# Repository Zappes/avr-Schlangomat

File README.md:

Der Schlangomat
===============

Was ist das?
------------
Der Schlangomat ist eine Kiste mit etwas Elektronik, ein paar Relais und zwei kombinierten Feuchtigkeits- und Temperatursensoren.
In der Kiste sind Steckdosen verbaut, die über Relais anhand gewisser Regeln an- und ausgeschaltet werden. Zusätzlich kann der
aktuelle Zustand der Dosen und Sensoren per WLAN abgefragt werden und die verschiedenen Betriebsparameter können mit einem
seriellen Terminal per USB programmiert werden.

Gedacht ist das ganze
als "Proof of Concept" für die Klimatisierung von Terrarien mit Schlangen drin - natürlich nur als Test und auf gar keinen fickenden
Fall für den tatsächlichen Einsatz. Ich bin schließlich kein Elektriker und baue deswegen keine Geräte, die mit Netzspannung
betrieben werden.

Was steckt so drin?
-------------------
Der Mikrocontroller ist ein ATmega32U4 von Atmel, der den USB-Controller schon drin hat. Für die WLAN-Anbindung wird ein ESP8266-03-Modul
benutzt, das mit der ganz normalen AT-Firmware läuft. Die Relais sind 36.11-Relais von Finder, die von einem ULN2003A angesteuert werden.

Output per http
---------------
Wenn man per http auf die IP des Geräts zugreift, kriegt man den folgenden Output zurück:

```
{"sock":[0,0,0,0],"sens":[{"h":45.9,"t":25.9,"e":0,"c":0},{"h":46.7,"t":26.2,"e":0,"c":0}],"rule":["T1 15 18","H1 32 38","T2 21 26","H2 34 50"]}
```

- sock: Der Zustand der Steckdosen von Dose 1 bis Dose 4. Im Beispiel ist nur die 3 an.
- sens: Die aktuellen Messwerte. h steht für die relative Luftfeuchtigkeit in Prozent, t für die Temperatur in °C, e für einen Errocode und c dafür, wie fot dieser Fehler jetzt in Folge aufgetreten ist.
- rule: Die aktuellen Regeln von Dose 1 bis Dose 4. Mehr dazu weiter unten.

Das Mistding schickt wirklich nur diesen Output, keine HTTP-Header. Hintergrund ist schlicht und ergreifend ein Bug in der
Firmware des WLAN-Moduls, wegen dem es nicht möglich ist, CRLF-Sequenzen zu schicken. Wer eine Lösung dafür findet, möge bitte
einen Pull-Request schicken ...

Intern werden die Sensoren nur etwa alle 5 Sekunden abgefragt. Wenn bei der Abfrage ein Fehler auftritt, steht dieser im Errorcode des Ergebnisses,
als Temperatur und Feuchtigkeit werden dann jeweils 0.0 gemeldet. Wenn der Fehler bei mehreren Abfragen in Forlge auftritt, steht in c die Anzahl
dieser Fehlversuche oder 255, wenn es schon mehr als 254 mal passiert ist. Was die genauen Fehlercodes bedeuten, kann man sich in lib/am2302.c
raussuchen, bei Code 4 kann man aber meistens davon ausgehen, dass der Sensor schlicht nicht eingesteckt ist. Oder total im Arsch.

USB-Kommandos
-------------

Wenn man ein USB-Kabel in das Gerät pöppelt, kann man sich mit einem seriellen Terminal verbinden. Als Verbindungsparameter sind 9600 8N1 zu verwenden, lokales Echo kann man sich schenken. Linuxer können das
beispielsweise so angehen:

```
minicom --device /dev/ttyACM0 -b 9600
```

Windowser verwenden vermutlich Putty oder Teraterm oder sowas.

In der seriellen Konsole hat man nun die folgenden Befehle:

| Befehl      | Parameter        | Beschreibung
|-------------|------------------|-------------
| espsetup    |                  | Initialisiert den WLAN-Chip.
| esp         | esp-kommando     | Führt ein ESP-Kommando aus - siehe weiter unten.
| setrule     | dose [regel]     | Setzt eine Regel für eine Dose, z.b. mit "setrule 1 T1 23 27". Ohne Regel wird die Regelausführung für die Dose deaktiviert
| getrule     | [dose]           | Gibt eine Regel aus. Ohne Parameter werden alle Regeln ausgegeben.
| on          | [dose]           | Schaltet eine Dose an. Wird die Dose nicht angegeben, werden alle Dosen aktiviert.
| off         | [dose]           | Schaltet eine Dose ab. Wird die Dose nicht angegeben, werden alle Dosen deaktiviert.
| state       |                  | Gibt den aktuellen Zustand der Dosen aus.
| sens        |                  | Gibt den aktuellen Zustand der Sensoren aus.
| setinterval | Sekunden         | Setzt das Intervall, in dem die Sensoren abgefragt und die Regeln ausgeführt werden.
| getinterval | Sekunden         | Zeigt das Intervall, in dem die Sensoren abgefragt und die Regeln ausgeführt werden, an.

Die Regelsyntax
---------------

Die Regeln beziehen sich immer auf eine Steckdose und können die jeweilige Dose abhängig von der Temperatur oder Luftfeuchtigkeit eines der beiden Sensoren messen. Das Format beim Setzen der Regel ist wie folgt:

```
setrule [Dose] [T|H][Sensor] [Minimum] [Maximum]
```

Angenommen, an Dose 3 hängt eine Heizung für das Terrarium, in dem Sensor 2 angebracht ist. Nun soll eine Regel die Temperatur zwischen 25 und 28 °C halten. Der entsprechende Befehl sieht wie folgt aus:

```
setrule 3 T2 25 28
```

Dabei ist zu beachten, dass die Firmware derzeit davon ausgeht, dass die Geräte an den Dosen die Messwerte ERHÖHEN, d.h. wie eine Heizung oder ein Befeuchter funktionieren. Würde man Kühlungen oder Entfeuchter anschließen wollen, wäre eine Firmware nötig, bei der man angeben kann, welche Wirkung die Geräte haben.

Die ESP-Befehle
---------------

Mit dem Befehl "esp" können Befehle an den ESP-Chip durchgereicht werden. Dabei ist zu beachten, dass das nur für die "normalen" Befehle funktioniert, die am Ende "OK" oder "ERR" ausgeben. Kompliziertes Zeug wie CIPSEND funktioniert so nicht, und die Ausgabe beim Reset ist zumindest eigentümlich.

Typischerweise braucht man die ESP-Befehle sowieso nur, um sich mit einem WLAN-AP zu verbinden. Dafür zeigt man sich erst mal mit ESP AT+CWLAP die Namen der APs an, dann verbindet man sich mittels ESP AT+CWJAP="SSID","PASS".

Die Frontplatte
---------------

Die Beschaltung der Frontplatte ist wie folgt:

Gibt es Videos?
-----------------------
[Natürlich gibt es eine Youtube-Playlist.](https://www.youtube.com/playlist?list=PLFFlJlvZ--PkRfQQ3qQJbDEAugWxiXpbW)

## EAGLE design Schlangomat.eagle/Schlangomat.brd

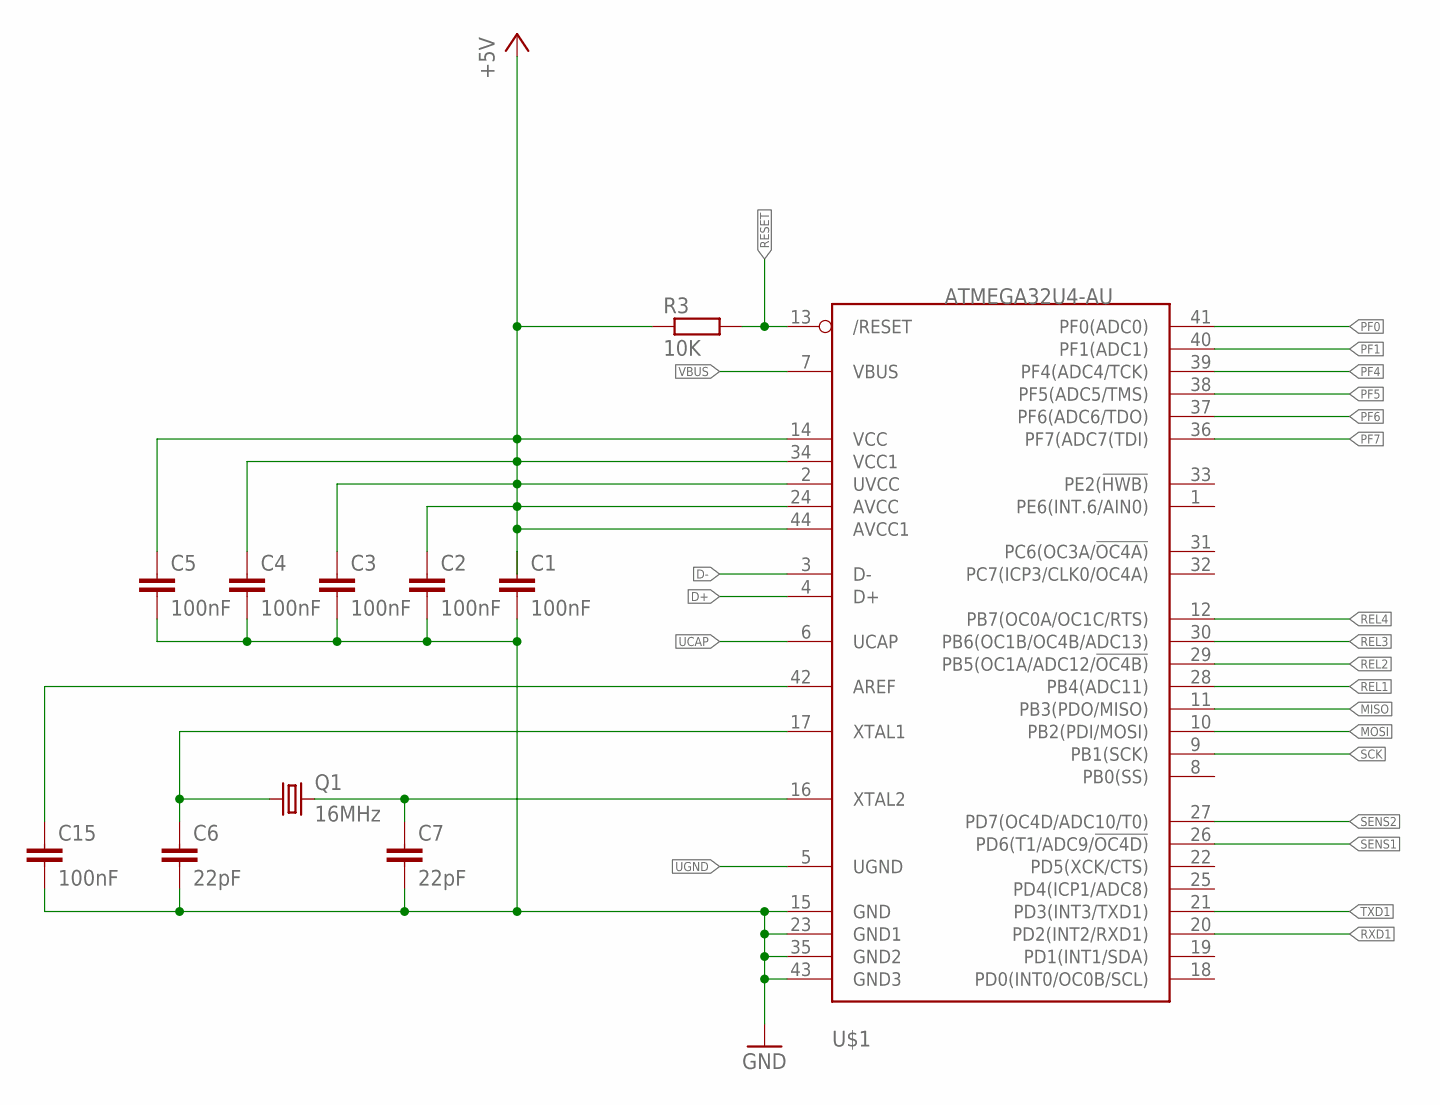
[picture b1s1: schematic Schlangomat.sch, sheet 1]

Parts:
C1, C2, C3, C4, C5, C15: 100nF; C0805
C6, C7: 22pF; C0805
Q1: 16MHz; HC49/S
R3: 10K; R0805
U$1: ATMEGA32U4-AU; TQFP44

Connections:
+5V: C1.1, C2.1, C3.1, C4.1, C5.1, R3.1, U$1.2 (UVCC), U$1.14 (VCC), U$1.24 (AVCC), U$1.34 (VCC1), U$1.44 (AVCC1); also elsewhere on the board
D+: U$1.4 (D+); also elsewhere on the board
D-: U$1.3 (D-); also elsewhere on the board
GND: C1.2, C2.2, C3.2, C4.2, C5.2, C6.2, C7.2, C15.2, U$1.15 (GND), U$1.23 (GND1), U$1.35 (GND2), U$1.43 (GND3); also elsewhere on the board
MISO: U$1.11 (PB3(PDO/MISO)); also elsewhere on the board
MOSI: U$1.10 (PB2(PDI/MOSI)); also elsewhere on the board
unnamed: C6.1, Q1.1, U$1.17 (XTAL1)
unnamed: C7.1, Q1.2, U$1.16 (XTAL2)
unnamed: C15.1, U$1.42 (AREF)
PF0: U$1.41 (PF0(ADC0)); also elsewhere on the board
PF1: U$1.40 (PF1(ADC1)); also elsewhere on the board
PF4: U$1.39 (PF4(ADC4/TCK)); also elsewhere on the board
PF5: U$1.38 (PF5(ADC5/TMS)); also elsewhere on the board
PF6: U$1.37 (PF6(ADC6/TDO)); also elsewhere on the board
PF7: U$1.36 (PF7(ADC7(TDI)); also elsewhere on the board
REL1: U$1.28 (PB4(ADC11)); also elsewhere on the board
REL2: U$1.29 (PB5(OC1A/ADC12/!OC4B)); also elsewhere on the board
REL3: U$1.30 (PB6(OC1B/OC4B/ADC13)); also elsewhere on the board
REL4: U$1.12 (PB7(OC0A/OC1C/RTS)); also elsewhere on the board
RESET: R3.2, U$1.13 (/RESET); also elsewhere on the board
RXD1: U$1.20 (PD2(INT2/RXD1)); also elsewhere on the board
SCK: U$1.9 (PB1(SCK)); also elsewhere on the board
SENS1: U$1.26 (PD6(T1/ADC9/!OC4D)); also elsewhere on the board
SENS2: U$1.27 (PD7(OC4D/ADC10/T0)); also elsewhere on the board
TXD1: U$1.21 (PD3(INT3/TXD1)); also elsewhere on the board
UCAP: U$1.6 (UCAP); also elsewhere on the board
UGND: U$1.5 (UGND); also elsewhere on the board
VBUS: U$1.7 (VBUS); also elsewhere on the board

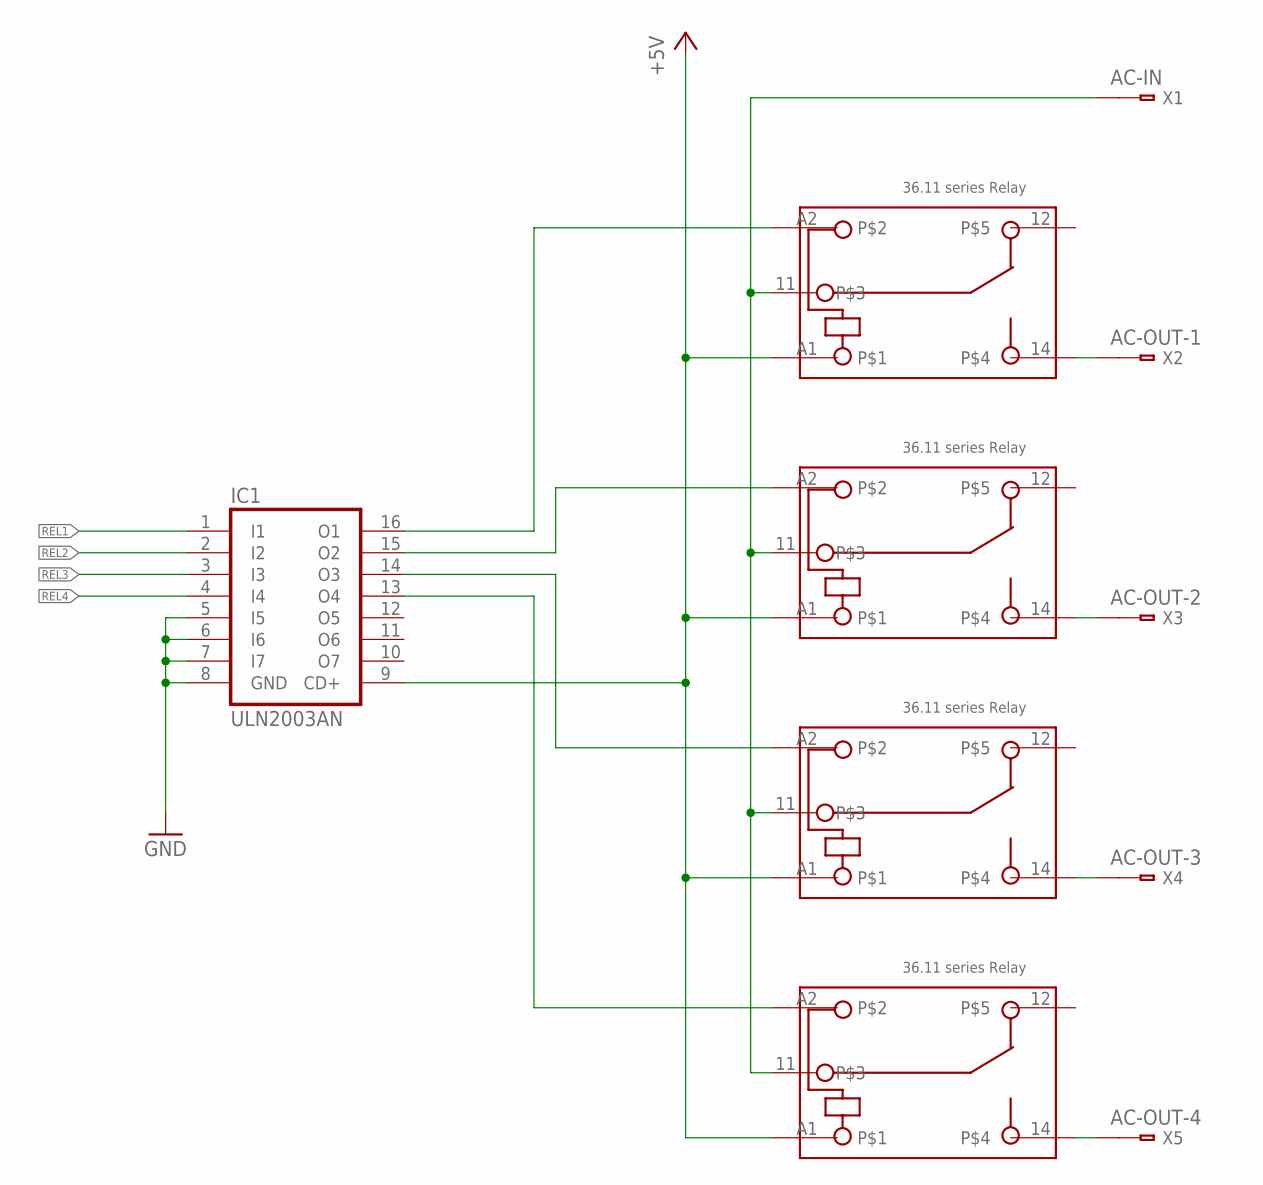
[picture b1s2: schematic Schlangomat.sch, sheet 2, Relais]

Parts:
IC1: ULN2003AN; DIL16
K1, K2, K3, K4: 36.11
X1: AC-IN; 236-5XX
X2: AC-OUT-1; 236-5XX
X3: AC-OUT-2; 236-5XX
X4: AC-OUT-3; 236-5XX
X5: AC-OUT-4; 236-5XX

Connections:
+5V: IC1.9 (CD+), K1.A1, K2.A1, K3.A1, K4.A1; also elsewhere on the board
AC_IN: K1.11, K2.11, K3.11, K4.11, X1.1@2 (B1)
GND: IC1.5 (I5), IC1.6 (I6), IC1.7 (I7), IC1.8 (GND); also elsewhere on the board
unnamed: IC1.16 (O1), K1.A2
unnamed: IC1.15 (O2), K2.A2
unnamed: IC1.14 (O3), K3.A2
unnamed: IC1.13 (O4), K4.A2
unnamed: K1.14, X2.1@2 (B1)
unnamed: K2.14, X3.1@2 (B1)
unnamed: K3.14, X4.1@2 (B1)
unnamed: K4.14, X5.1@2 (B1)
REL1: IC1.1 (I1); also elsewhere on the board
REL2: IC1.2 (I2); also elsewhere on the board
REL3: IC1.3 (I3); also elsewhere on the board
REL4: IC1.4 (I4); also elsewhere on the board

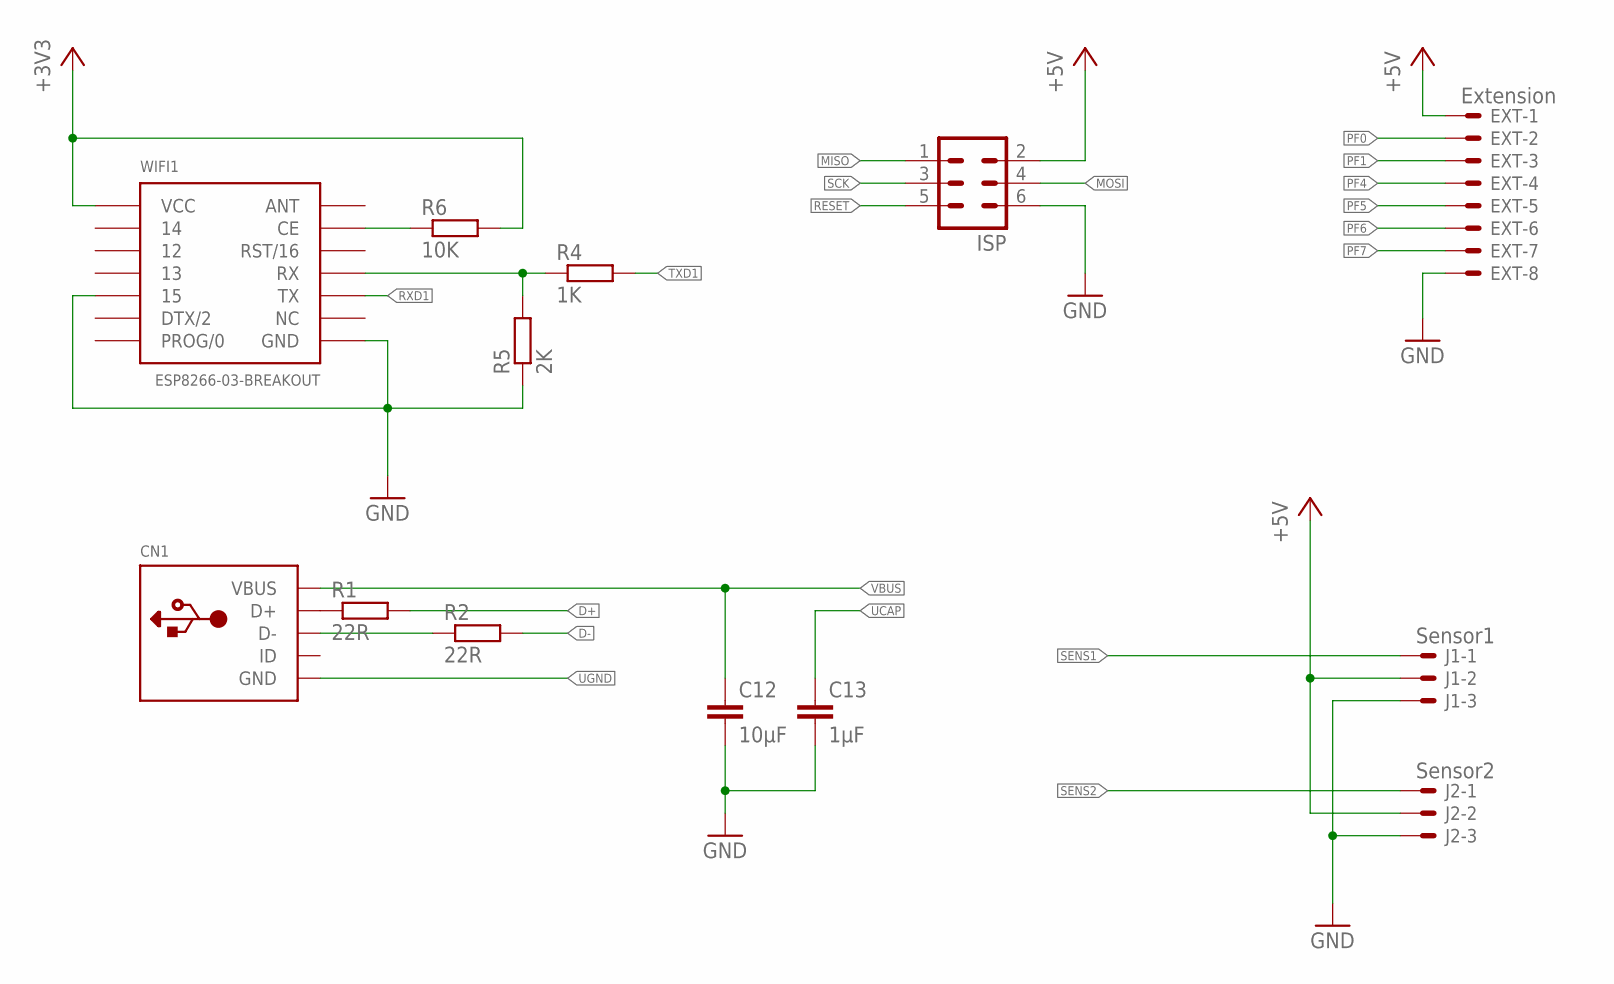
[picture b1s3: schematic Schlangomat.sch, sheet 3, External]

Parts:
C12: 10µF; C0805
C13: 1µF; C0805
CN1: USBMOLEX; USB-MINIB-THM-MOLEX
EXT: Extension; 6410-08
ISP: ML6
J1: Sensor1; 6410-03
J2: Sensor2; 6410-03
R1, R2: 22R; R0805
R4: 1K; R0805
R5: 2K; R0805
R6: 10K; R0805
WIFI1: ESP8266-03-BREAKOUT; ESP-03-BREAKOUT

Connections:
+3V3: R6.2, WIFI1.VCC; also elsewhere on the board
+5V: EXT.1, ISP.2, J1.2, J2.2; also elsewhere on the board
D+: R1.2; also elsewhere on the board
D-: R2.2; also elsewhere on the board
GND: C12.2, C13.2, EXT.8, ISP.6, J1.3, J2.3, R5.1, WIFI1.15, WIFI1.GND; also elsewhere on the board
MISO: ISP.1; also elsewhere on the board
MOSI: ISP.4; also elsewhere on the board
unnamed: CN1.D+, R1.1
unnamed: CN1.D-, R2.1
unnamed: R6.1, WIFI1.CE
PF0: EXT.2; also elsewhere on the board
PF1: EXT.3; also elsewhere on the board
PF4: EXT.4; also elsewhere on the board
PF5: EXT.5; also elsewhere on the board
PF6: EXT.6; also elsewhere on the board
PF7: EXT.7; also elsewhere on the board
RESET: ISP.5; also elsewhere on the board
RXD1: WIFI1.TX; also elsewhere on the board
SCK: ISP.3; also elsewhere on the board
SENS1: J1.1; also elsewhere on the board
SENS2: J2.1; also elsewhere on the board
TXD1: R4.1, R4.2, R5.2, WIFI1.RX; also elsewhere on the board
UCAP: C13.1; also elsewhere on the board
UGND: CN1.GND; also elsewhere on the board
VBUS: C12.1, CN1.VBUS; also elsewhere on the board

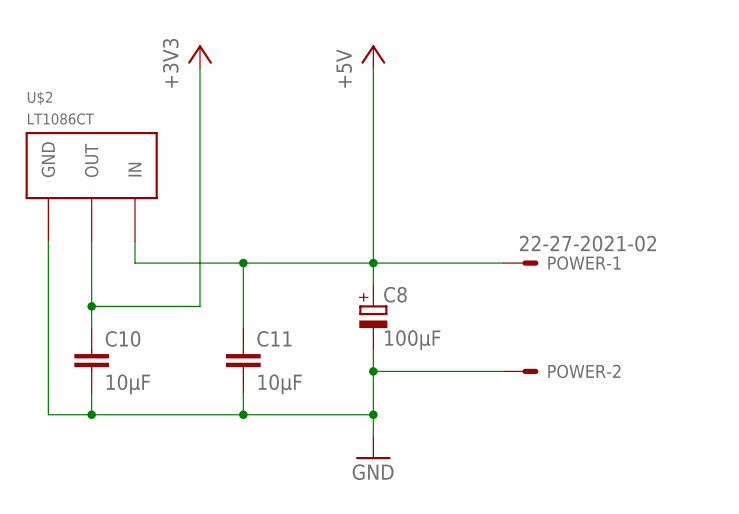
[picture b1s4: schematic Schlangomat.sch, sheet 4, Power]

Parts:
C8: 100µF; UD-5X5,8_NICHICON
C10, C11: 10µF; C0805
POWER: 22-27-2021-02; 6410-02
U$2: LT1086CT; TO220V

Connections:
+3V3: C10.1, U$2.2 (OUT); also elsewhere on the board
+5V: C8.+, C11.1, POWER.1, U$2.3 (IN); also elsewhere on the board
GND: C8.-, C10.2, C11.2, POWER.2, U$2.1 (GND); also elsewhere on the board

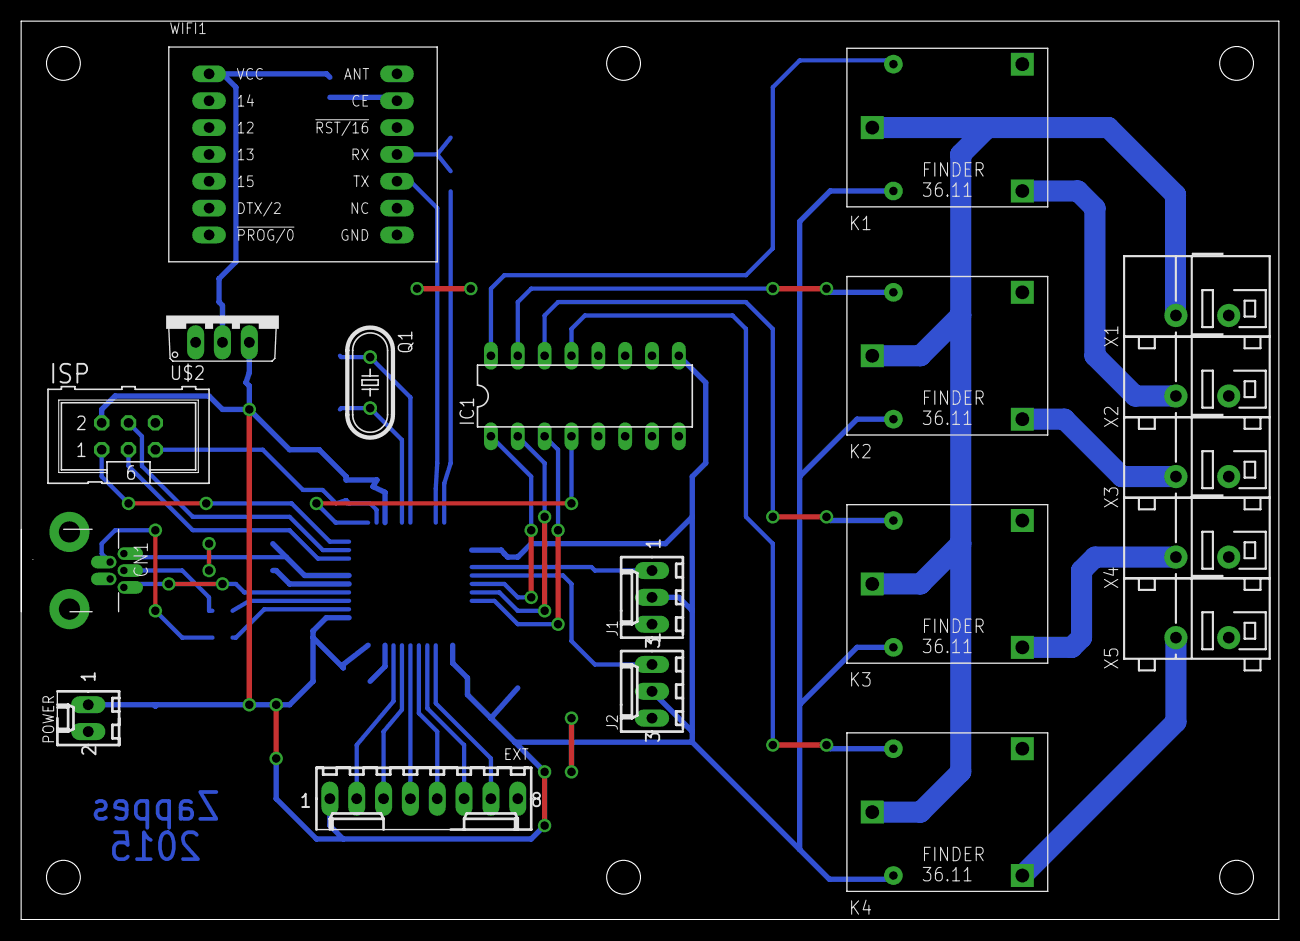
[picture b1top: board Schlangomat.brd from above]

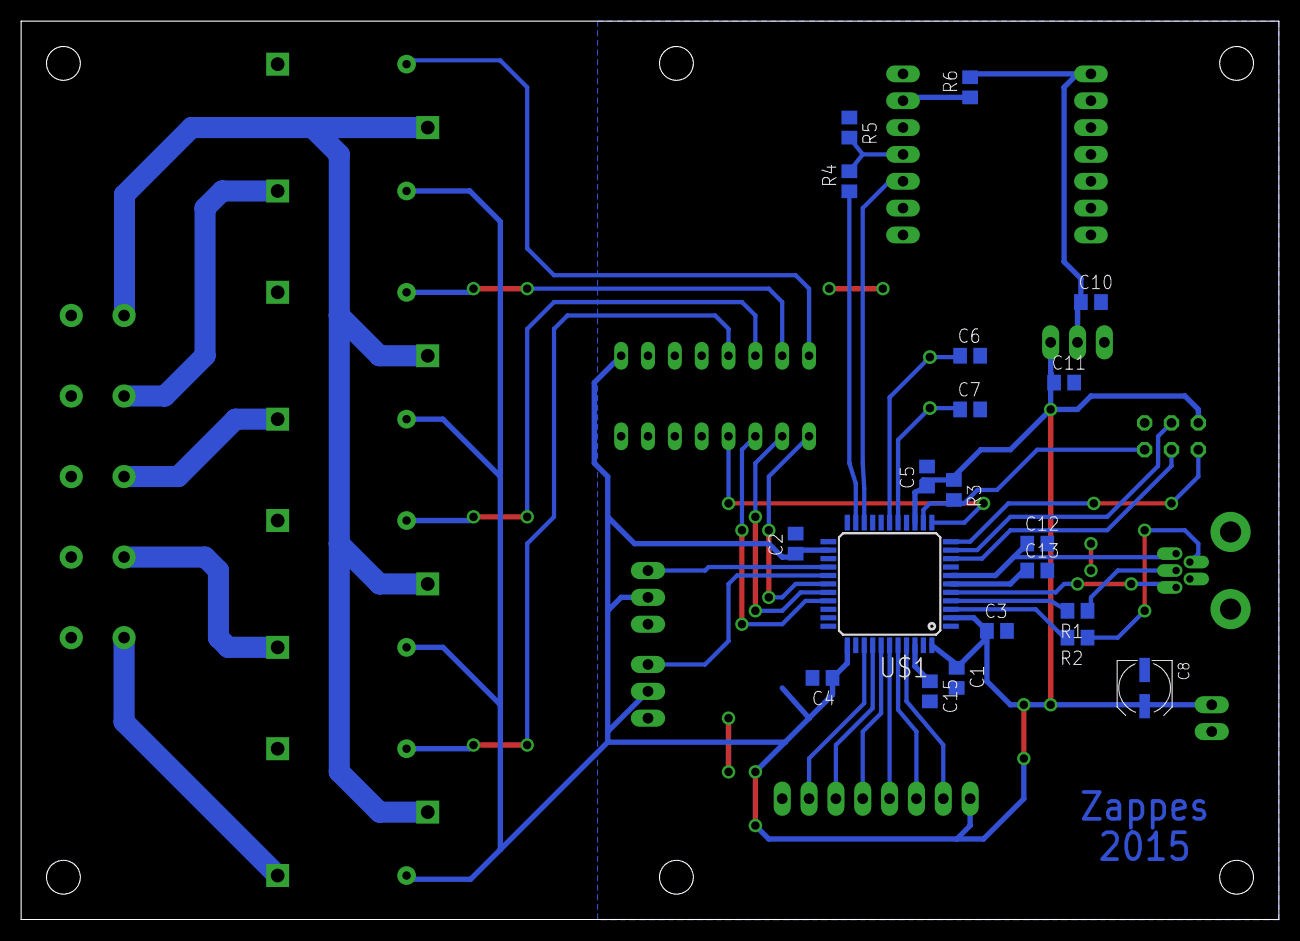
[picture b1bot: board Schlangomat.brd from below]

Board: 2 copper layers, 119.0 x 85.0 mm, 39 parts (20 on the bottom side), 41 nets.

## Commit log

2015-04-19 Lib für den Sensor hinzugefügt
2015-04-19 Sensor-Support eingebaut
2015-04-29 Board gelayoutet
2015-05-03 Relaissteuerung und Parser in eigene Files verlagert, allgemeinen Verbesserungen.
2015-05-10 PullUp-FuckUp gefixt, Fehlerbeseitigt
2015-05-24 Timerbasierte Abfrage der Sensoren eingebaut
2015-05-24 Timerbasierte Regelausführung
2015-05-26 Regelsyntax geändert, Ausführung und Hysterese implementiert
2015-05-31 Parseroptinmierungen und neues Regelformat
2015-06-06 Erste Arbeit am HTTP-Modul.
2015-06-07 Lesen von USB und ESP erheblich vereinfacht, verwendung eines ESP-Handlers für die Reaktion auf HTTP-Requests vorbereitet.
2015-06-13 Code für die Ausführung von ESP-Kommandos überarbeitet.
2015-06-22 Webserver primtiiv implementiert - auf jeden Request kommt ein JSON-String mit den Sensorwerten und Relaiszuständen zurück.
2015-06-23 Fixes am Netzwerkcode und Persistierung der Regeln im EEPROM
2015-06-23 Optimierungen bei Makefile und Persistierung
2015-06-30 Kleinkram im Zuge der Beta-Auslieferung
2015-06-30 README ins richtige Verzeichnis gelegt
2015-06-30 Doku erweitert, Bilder hinzugefügt
2015-06-30 Bild in die README eingebaut
